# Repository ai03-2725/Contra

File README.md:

# Contra
Extremely low cost ortholinear keyboard

The bare minimum for a functional keyboard.

#### In light of recent claims that I am 100% liable for any of my open source PCBs, I am adding this disclaimer.
#### I provide these PCBs as a reference for designing keyboard PCBs. Using them within your projects will require a will to do research of one's own and to learn the workings of them, potentially fixing issues if they exist.
# I provide these PCBs without liability and without any guarantees regarding functionality, as expressed in the MIT license under which all of these PCBs are licensed.

### Features
- 2U or split space.
- All through-hole parts. 48x diodes, 1x Pro Micro.
- Assembled by M2 standoffs and screws.
- Programmable via firmware of choice, such as TMK.
- Nothing fancy. A very nice way to try out some switches, enjoy some DIY, or to test out ortho keyboards.

### Parts list
- 48x 1N4148 diodes or similar, THT
- 1x Pro Micro
- 48x Switches
- Optional 1x 2U stabilizer, PCB mount
- One PCB, one plate, and one bottom plate
- 5 M2 8mm standoffs
- 10 M2 screws

### Files for production
- Main PCB: Check the [latest releases](https://github.com/ai03-2725/Contra/releases), or grab the latest gerber [here](https://github.com/ai03-2725/Contra/blob/master/Gerbers/Gerbers.zip).
- Case files: Check the case repo [here](https://github.com/ai03-2725/ContraPlates).

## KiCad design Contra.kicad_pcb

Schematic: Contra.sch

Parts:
D1, D2, D3, D4, D5, D6, D7, D8, D9, D10, D11, D12, D13, D14, D15, D16, D17, D18, D19, D20, D21, D22, D23, D24, D25, D26, D27, D28, D29, D30, D31, D32, D33, D34, D35, D36, D37, D38, D39, D40, D41, D42, D43, D44, D45, D46, D47, D48: 1N4148; D_DO-35_SOD27_P7.62mm_Horizontal-DoubleSided
J1: Conn_01x04; Pin_Header_Straight_1x04_Pitch2.54mm
MX1, MX2, MX3, MX4, MX5, MX6, MX7, MX8, MX9, MX10, MX11, MX12, MX13, MX14, MX15, MX16, MX17, MX18, MX19, MX20, MX21, MX22, MX23, MX24, MX25, MX26, MX27, MX28, MX29, MX30, MX31, MX32, MX33, MX34, MX35, MX36, MX37, MX38, MX39, MX40, MX41, MX42, MX43, MX44, MX45, MX46, MX47, MX48: MX-1U; MX-1U-NoLED
MX49: MX-2U; MX-2U-ReversedStabilizers-NoLED
SW1: SW_PUSH; PushButton_6x6mm_TH_Pretty
U1: ProMicro; pro_micro

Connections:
+5V: J1.4, U1.21 (5V)
COL0: MX1.1 (COL), MX13.1 (COL), MX25.1 (COL), MX37.1 (COL), U1.20 (21)
COL1: MX2.1 (COL), MX14.1 (COL), MX26.1 (COL), MX38.1 (COL), U1.19 (20)
COL2: MX3.1 (COL), MX15.1 (COL), MX27.1 (COL), MX39.1 (COL), U1.12 (9)
COL3: MX4.1 (COL), MX16.1 (COL), MX28.1 (COL), MX40.1 (COL), U1.11 (8)
COL4: MX5.1 (COL), MX17.1 (COL), MX29.1 (COL), MX41.1 (COL), U1.10 (7)
COL5: MX6.1 (COL), MX18.1 (COL), MX30.1 (COL), MX42.1 (COL), MX49.1 (COL), U1.9 (6)
COL6: MX7.1 (COL), MX19.1 (COL), MX31.1 (COL), MX43.1 (COL), U1.8 (5)
COL7: MX8.1 (COL), MX20.1 (COL), MX32.1 (COL), MX44.1 (COL), U1.7 (4)
COL8: MX9.1 (COL), MX21.1 (COL), MX33.1 (COL), MX45.1 (COL), U1.6 (3)
COL9: MX10.1 (COL), MX22.1 (COL), MX34.1 (COL), MX46.1 (COL), U1.5 (2)
COL10: MX11.1 (COL), MX23.1 (COL), MX35.1 (COL), MX47.1 (COL), U1.2 (0)
COL11: MX12.1 (COL), MX24.1 (COL), MX36.1 (COL), MX48.1 (COL), U1.1
GND: J1.1, SW1.2, U1.3 (GND), U1.4 (GND), U1.23 (GND)
unnamed: D1.2 (A), MX1.2 (ROW)
unnamed: D2.2 (A), MX2.2 (ROW)
unnamed: D3.2 (A), MX3.2 (ROW)
unnamed: D4.2 (A), MX4.2 (ROW)
unnamed: D5.2 (A), MX5.2 (ROW)
unnamed: D6.2 (A), MX6.2 (ROW)
unnamed: D7.2 (A), MX7.2 (ROW)
unnamed: D8.2 (A), MX8.2 (ROW)
unnamed: D9.2 (A), MX9.2 (ROW)
unnamed: D10.2 (A), MX10.2 (ROW)
unnamed: D11.2 (A), MX11.2 (ROW)
unnamed: D12.2 (A), MX12.2 (ROW)
unnamed: D13.2 (A), MX13.2 (ROW)
unnamed: D14.2 (A), MX14.2 (ROW)
unnamed: D15.2 (A), MX15.2 (ROW)
unnamed: D16.2 (A), MX16.2 (ROW)
unnamed: D17.2 (A), MX17.2 (ROW)
unnamed: D18.2 (A), MX18.2 (ROW)
unnamed: D19.2 (A), MX19.2 (ROW)
unnamed: D20.2 (A), MX20.2 (ROW)
unnamed: D21.2 (A), MX21.2 (ROW)
unnamed: D22.2 (A), MX22.2 (ROW)
unnamed: D23.2 (A), MX23.2 (ROW)
unnamed: D24.2 (A), MX24.2 (ROW)
unnamed: D25.2 (A), MX25.2 (ROW)
unnamed: D26.2 (A), MX26.2 (ROW)
unnamed: D27.2 (A), MX27.2 (ROW)
unnamed: D28.2 (A), MX28.2 (ROW)
unnamed: D29.2 (A), MX29.2 (ROW)
unnamed: D30.2 (A), MX30.2 (ROW)
unnamed: D31.2 (A), MX31.2 (ROW)
unnamed: D32.2 (A), MX32.2 (ROW)
unnamed: D33.2 (A), MX33.2 (ROW)
unnamed: D34.2 (A), MX34.2 (ROW)
unnamed: D35.2 (A), MX35.2 (ROW)
unnamed: D36.2 (A), MX36.2 (ROW)
unnamed: D37.2 (A), MX37.2 (ROW)
unnamed: D38.2 (A), MX38.2 (ROW)
unnamed: D39.2 (A), MX39.2 (ROW)
unnamed: D40.2 (A), MX40.2 (ROW)
unnamed: D41.2 (A), MX41.2 (ROW)
unnamed: D42.2 (A), MX42.2 (ROW), MX49.2 (ROW)
unnamed: D43.2 (A), MX43.2 (ROW)
unnamed: D44.2 (A), MX44.2 (ROW)
unnamed: D45.2 (A), MX45.2 (ROW)
unnamed: D46.2 (A), MX46.2 (ROW)
unnamed: D47.2 (A), MX47.2 (ROW)
unnamed: D48.2 (A), MX48.2 (ROW)
unnamed: SW1.1, U1.22 (RST)
PIN15: J1.2, U1.16 (15)
PIN18: J1.3, U1.17 (18)
ROW0: D1.1 (K), D2.1 (K), D3.1 (K), D4.1 (K), D5.1 (K), D6.1 (K), D7.1 (K), D8.1 (K), D9.1 (K), D10.1 (K), D11.1 (K), D12.1 (K), U1.18 (19)
ROW1: D13.1 (K), D14.1 (K), D15.1 (K), D16.1 (K), D17.1 (K), D18.1 (K), D19.1 (K), D20.1 (K), D21.1 (K), D22.1 (K), D23.1 (K), D24.1 (K), U1.15 (14)
ROW2: D25.1 (K), D26.1 (K), D27.1 (K), D28.1 (K), D29.1 (K), D30.1 (K), D31.1 (K), D32.1 (K), D33.1 (K), D34.1 (K), D35.1 (K), D36.1 (K), U1.14 (16)
ROW3: D37.1 (K), D38.1 (K), D39.1 (K), D40.1 (K), D41.1 (K), D42.1 (K), D43.1 (K), D44.1 (K), D45.1 (K), D46.1 (K), D47.1 (K), D48.1 (K), U1.13 (10)

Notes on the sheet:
Contra low-cost ortholinear mechanical keyboard
1 1
I forgot
1.something

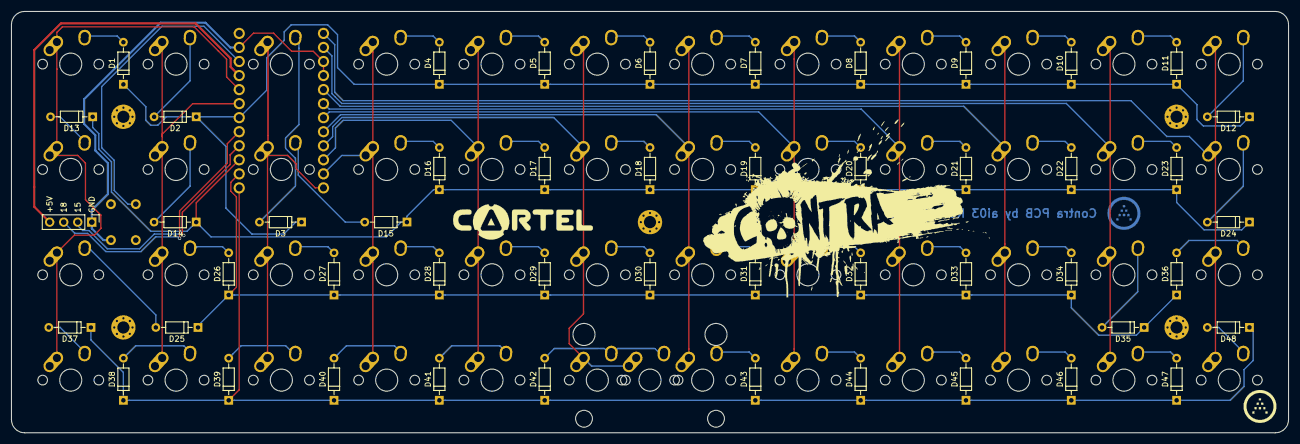
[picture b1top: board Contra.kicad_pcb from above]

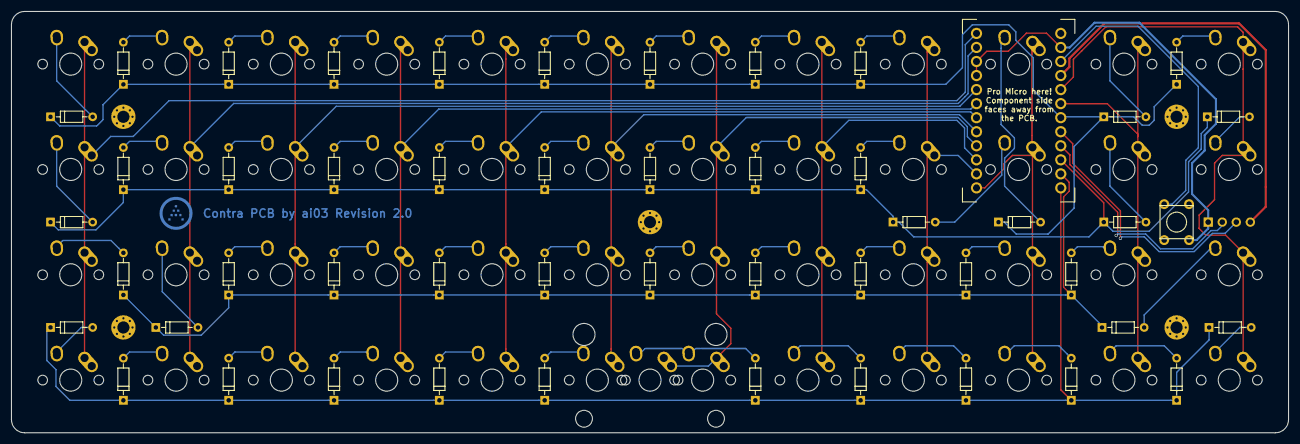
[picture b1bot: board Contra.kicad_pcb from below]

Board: 2 copper layers, 231.0 x 76.2 mm, 100 parts (2 on the bottom side), 69 nets.

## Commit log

2017-12-06 :lollipop: Added .gitattributes & .gitignore files
2017-12-06 Add submods
2017-12-06 Add local libs
2017-12-06 Begin schematic
2017-12-06 Finish schematic
    Well... that was fast
2017-12-06 Begin building pcb
2017-12-06 row 3 is in
2017-12-06 Finish grid
2017-12-07 Finish the dank memes
2017-12-07 Generate gerbers
2017-12-07 Plot dimensions for drilling reset hole in bottom
2017-12-07 Fix DRC error, update gerbers
2017-12-08 Unroute for moving pmicro
2017-12-08 Finish reroute
2017-12-08 Make gnd plane flow better
2017-12-08 Update gerbers
2017-12-09 Update some memes
2017-12-09 New gerbs
2017-12-14 breakout pins
2017-12-14 Update gerber
2017-12-14 REEEEEE
2017-12-20 Add memes and update gerber
2017-12-22 Update footprints for silk
2017-12-22 Reposition memes, add you won't download...
2017-12-22 New gerbers
2018-01-14 Remove some images
2018-01-14 Revert "Remove some images"
    This reverts commit 0baf5fd5442c26d070a6e67100257904d2560f5a.
2018-01-14 Improve routing, add broken image
2018-01-14 Update some routing
2018-01-15 Remove some artworkr
2018-01-16 Add de wey
2018-01-16 Plot new width dimensions
2018-01-16 Extend board on each side
2018-01-16 Update revisions, update gerbers
2018-02-09 Generate RS-274-X gerbers
2018-03-17 Rename project files
2018-04-03 No silk gerber created
2018-04-03 Update footprints to latest
2018-04-03 Fix issues present in R1
    - Diode silkscreen conflict fixed
    - Fix pinout on RGB breakout
    - Update footprints to Rev2
2018-04-03 Generate new gerbers
2018-11-27 Unroute, prepare for reroute
2018-11-27 Revert "Unroute, prepare for reroute"
    This reverts commit 2692a349e5744fa5fd6682816f15a667edd49ab0.
2018-11-27 Opt to reroute instead of rebuild from scratch
2018-11-27 Repair the mess of questionable routing decisions
2018-11-27 Convert to KiCad 5
2018-11-27 Update locallib
2018-11-27 Make diodes double sided
2018-11-27 Much needed submodule updates
